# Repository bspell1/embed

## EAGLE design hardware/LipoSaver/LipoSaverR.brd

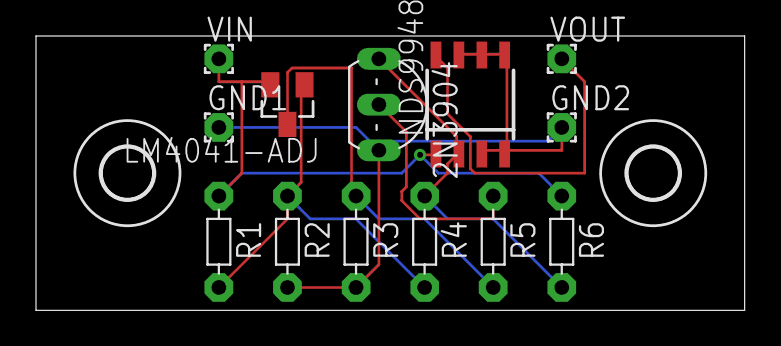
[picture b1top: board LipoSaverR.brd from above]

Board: 2 copper layers, 39.4 x 15.2 mm, 15 parts (0 on the bottom side), 7 nets.

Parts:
2N3904: TO92-EBC
E$40, E$42: 2,8
GND1, GND2: 1,6/0,8
LM4041-ADJ: SOT23
NDS9948: SOIC8
R1: R1; R-5
R2: R2; R-5
R3: 10K; R-5
R4: 4.7M; R-5
R5: 100K; R-5
R6: 20K; R-5
VIN: 1,6/0,8
VOUT: 1,6/0,8

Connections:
S$1: 2N3904.E, GND1.1, GND2.1, NDS9948.3, NDS9948.4, NDS9948.5, NDS9948.6, NDS9948.7, R2.2, R3.2
S$2: LM4041-ADJ.2, NDS9948.1, R1.1, R6.1, VIN.1
S$3: LM4041-ADJ.3, R3.1, R5.2
S$4: 2N3904.C, NDS9948.2, R4.1, R6.2
S$5: 2N3904.B, R5.1
S$6: NDS9948.8, VOUT.1
S$11: LM4041-ADJ.1, R1.2, R2.1, R4.2

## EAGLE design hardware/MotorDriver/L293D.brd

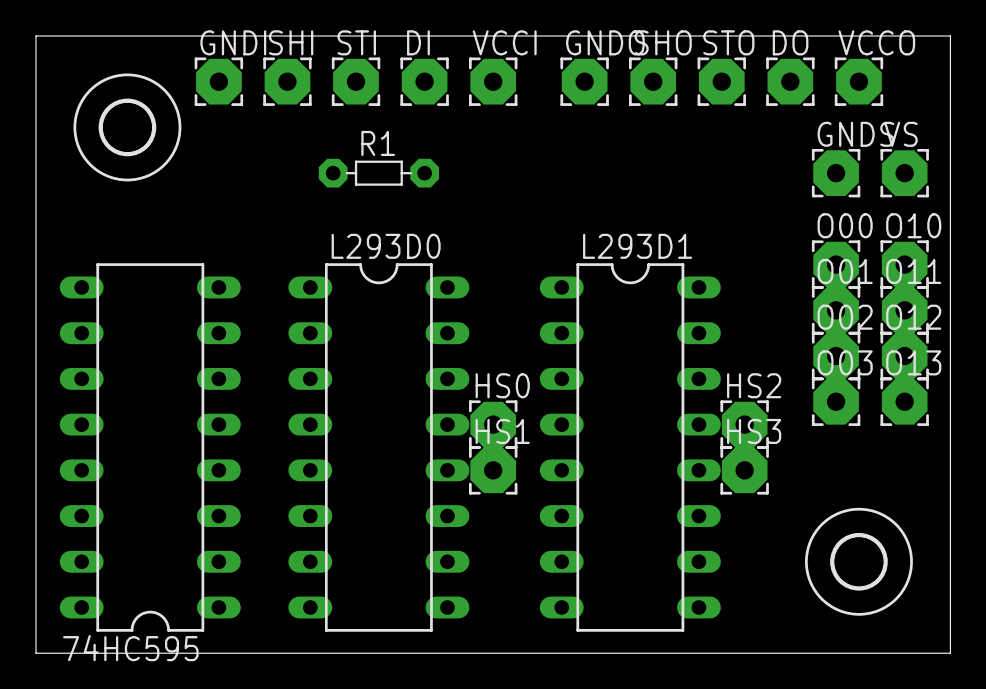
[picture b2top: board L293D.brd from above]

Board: 2 copper layers, 50.8 x 34.3 mm, 30 parts (0 on the bottom side), 24 nets, no tracks yet.

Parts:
74HC595: DIL16
DI: 2,54/1,0
DO: 2,54/1,0
E$1, E$2: 2,8
GNDI: 2,54/1,0
GNDO: 2,54/1,0
GNDS: 2,54/1,0
HS0, HS1, HS2, HS3: 2,54/1,0
L293D0, L293D1: DIL16
O00, O01, O02, O03, O10, O11, O12, O13: 2,54/1,0
R1: 10K; R-5
SHI: 2,54/1,0
SHO: 2,54/1,0
STI: 2,54/1,0
STO: 2,54/1,0
VCCI: 2,54/1,0
VCCO: 2,54/1,0
VS: 2,54/1,0

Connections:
GND: 74HC595.8, 74HC595.13, GNDI.1, GNDO.1, GNDS.1, HS0.1, HS1.1, HS2.1, HS3.1, L293D0.4, L293D0.5, L293D0.12, L293D0.13, L293D1.4, L293D1.5, L293D1.12, L293D1.13
S$1: 74HC595.10, L293D0.1, L293D0.9, L293D1.1, L293D1.9, R1.2
S$2: 74HC595.11, SHI.1, SHO.1
S$3: 74HC595.12, STI.1, STO.1
S$4: L293D0.8, L293D1.8, VS.1
S$5: 74HC595.14, DI.1
S$6: 74HC595.9, DO.1
S$7: 74HC595.15, L293D0.2
S$8: 74HC595.1, L293D0.7
S$9: 74HC595.2, L293D0.10
S$10: 74HC595.3, L293D0.15
S$11: L293D0.3, O00.1
S$12: L293D0.6, O01.1
S$13: L293D0.11, O02.1
S$14: L293D0.14, O03.1
S$15: 74HC595.4, L293D1.2
S$16: 74HC595.5, L293D1.7
S$17: 74HC595.6, L293D1.10
S$18: 74HC595.7, L293D1.15
S$19: L293D1.3, O10.1
S$20: L293D1.6, O11.1
S$21: L293D1.11, O12.1
S$22: L293D1.14, O13.1
W1: 74HC595.16, L293D0.16, L293D1.16, R1.1, VCCI.1, VCCO.1

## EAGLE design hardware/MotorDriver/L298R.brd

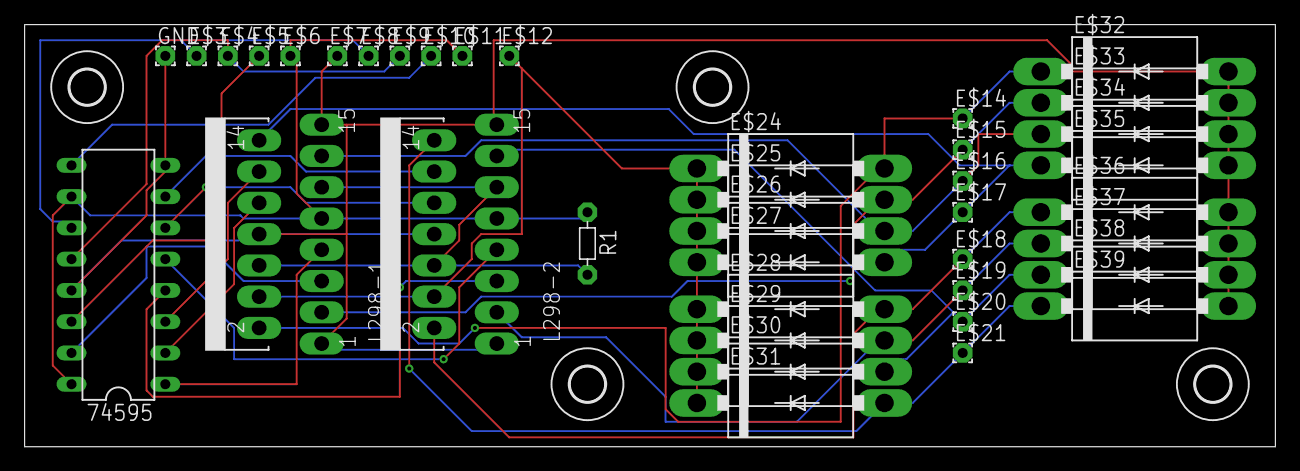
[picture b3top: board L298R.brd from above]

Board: 2 copper layers, 101.6 x 34.3 mm, 43 parts (0 on the bottom side), 24 nets.

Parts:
74595: 74595; DIL16
E$1, E$40, E$41, E$42: 2,8
E$3, E$4, E$5, E$6, E$7, E$8, E$9, E$10, E$11, E$12, E$14, E$15, E$16, E$17, E$18, E$19, E$20, E$21: 1,6/0,8
E$24, E$25, E$26, E$27, E$28, E$29, E$30, E$31, E$32, E$33, E$34, E$35, E$36, E$37, E$38, E$39: DO201-15
GND: 1,6/0,8
L298-1, L298-2: L298; MULTIWATT-15
R1: 10K; R-5

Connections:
S$1: 74595.8, 74595.13, E$7.1, E$32.A, E$33.A, E$34.A, E$35.A, E$36.A, E$37.A, E$38.A, E$39.A, GND.1, L298-1.1, L298-1.8, L298-1.15, L298-2.1, L298-2.8, L298-2.15
S$2: 74595.10, 74595.16, E$6.1, E$11.1, L298-1.9, L298-2.9, R1.1
S$3: 74595.11, E$3.1, E$8.1
S$4: 74595.12, E$4.1, E$9.1
S$5: 74595.14, E$5.1
S$6: 74595.9, E$10.1
S$7: E$14.1, E$24.A, E$32.C, L298-1.2
S$8: E$15.1, E$25.A, E$33.C, L298-1.3
S$9: E$12.1, E$24.C, E$25.C, E$26.C, E$27.C, E$28.C, E$29.C, E$30.C, E$31.C, L298-1.4, L298-2.4
S$10: 74595.15, L298-1.5
S$11: L298-1.6, L298-1.11, L298-2.6, L298-2.11, R1.2
S$12: 74595.1, L298-1.7
S$13: 74595.2, L298-1.10
S$14: 74595.3, L298-1.12
S$15: E$16.1, E$26.A, E$34.C, L298-1.13
S$16: E$17.1, E$27.A, E$35.C, L298-1.14
S$17: E$18.1, E$28.A, E$36.C, L298-2.2
S$18: E$19.1, E$29.A, E$37.C, L298-2.3
S$19: E$20.1, E$30.A, E$38.C, L298-2.13
S$20: E$21.1, E$31.A, E$39.C, L298-2.14
S$21: 74595.4, L298-2.5
S$22: 74595.5, L298-2.7
S$23: 74595.6, L298-2.10
S$24: 74595.7, L298-2.12

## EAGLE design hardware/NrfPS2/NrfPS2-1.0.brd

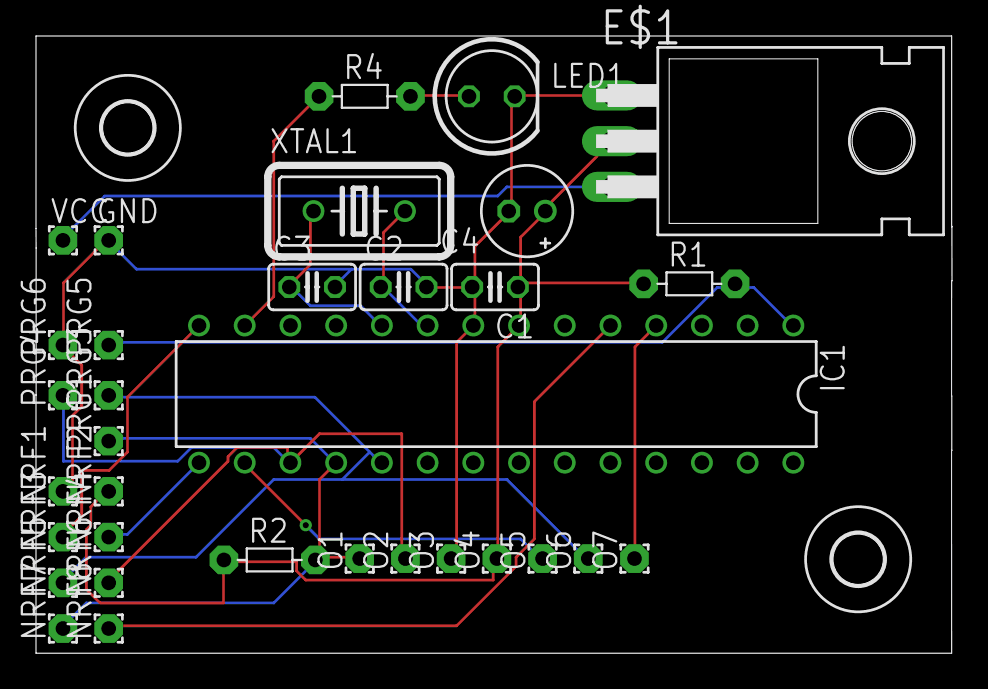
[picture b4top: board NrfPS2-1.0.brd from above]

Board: 2 copper layers, 50.9 x 34.3 mm, 35 parts (0 on the bottom side), 16 nets.

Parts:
C1, C2, C3: C025-025X050
C4: E2-5
E$1: TO220H
E$2, E$14: 2,8
GND: 1,6/0,8
IC1: PDIP-T28
LED1: LED5MM
NRF1, NRF2, NRF3, NRF4, NRF5, NRF6, NRF7, NRF8: 1,6/0,8
O1, O2, O3, O4, O5, O6, O7: 1,6/0,8
PRG1, PRG3, PRG4, PRG5, PRG6: 1,6/0,8
R1, R2, R4: R-5
VCC: 1,6/0,8
XTAL1: HC18U-V

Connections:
S$2: C1.2, C2.2, C3.2, C4.-, E$1.1, GND.1, IC1.8, LED1.K, NRF1.1, O3.1, PRG6.1
S$3: E$1.3, VCC.1
S$5: IC1.13, R4.1
S$6: C2.1, IC1.9, XTAL1.2
S$7: C3.1, IC1.10, XTAL1.1
S$8: IC1.1, PRG5.1, R1.2
S$9: IC1.18, NRF7.1, O1.1, PRG1.1, R2.2
S$10: C1.1, C4.+, E$1.2, IC1.7, NRF2.1, O4.1, R1.1, R2.1
S$11: IC1.15, NRF4.1
S$12: IC1.19, NRF5.1, O6.1, PRG3.1
S$13: IC1.17, NRF6.1, O2.1, PRG4.1
S$14: IC1.14, NRF3.1
S$15: IC1.16, O5.1
S$16: IC1.4, O7.1
S$18: IC1.5, NRF8.1
S$22: LED1.A, R4.2

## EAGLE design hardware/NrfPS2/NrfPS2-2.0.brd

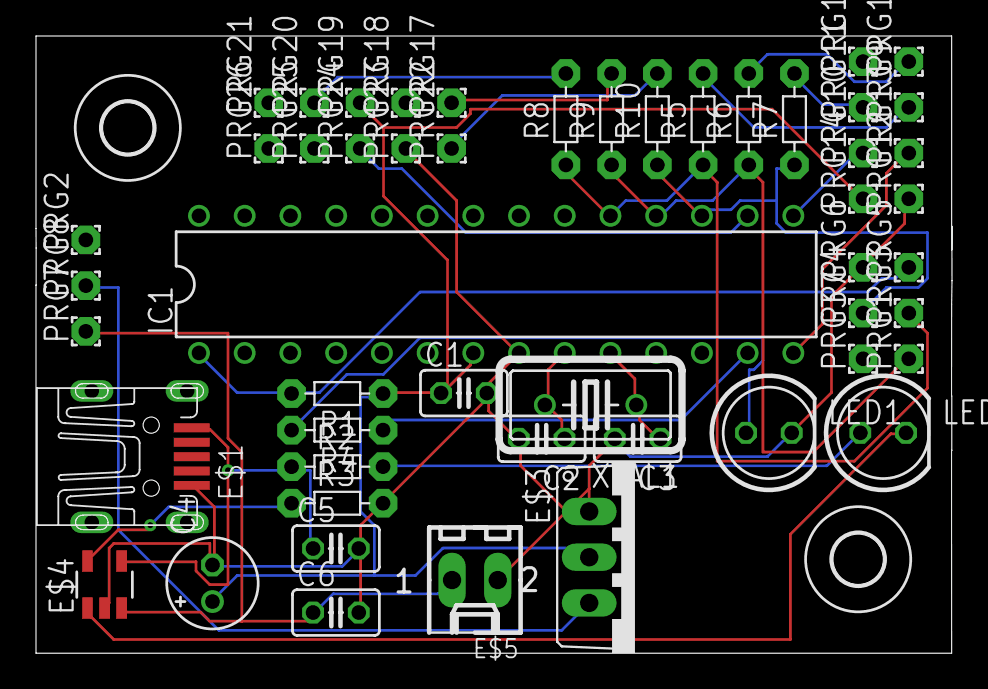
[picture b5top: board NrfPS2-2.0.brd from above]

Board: 2 copper layers, 50.9 x 34.3 mm, 53 parts (0 on the bottom side), 25 nets.

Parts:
C1, C2, C3, C5, C6: C025-025X050
C4: E2-5
E$1: UX60-MB-5S8
E$2, E$14: 2,8
E$3: TO220V
E$4: SOT23-5
E$5: 6410-02
IC1: PDIP-T28
LED1, LED2: LED5MM
PRG1, PRG2, PRG3, PRG4, PRG5, PRG6, PRG7, PRG8, PRG9, PRG10, PRG11, PRG12, PRG13, PRG14, PRG15, PRG16, PRG17, PRG18, PRG19, PRG20, PRG21, PRG22, PRG23, PRG24, PRG25, PRG26, PRG37: 1,6/0,8
R1, R2, R3, R4, R5, R6, R7, R8, R9, R10: R-5
XTAL1: HC18U-V

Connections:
S$2: C1.2, C2.2, C3.2, C4.-, C5.2, C6.2, E$1.5, E$3.1, E$4.2, E$5.2, IC1.8, LED1.K, PRG6.1, PRG12.1, PRG23.1, R3.2
S$3: E$4.1, LED2.K
S$5: IC1.13, R4.1
S$6: C2.1, IC1.9, XTAL1.2
S$7: C3.1, IC1.10, XTAL1.1
S$8: IC1.1, PRG5.1, R1.2
S$9: IC1.18, PRG1.1, R6.1, R9.1
S$10: C1.1, C4.+, E$3.2, IC1.7, PRG14.1, PRG19.1, R1.1
S$11: IC1.15, PRG10.1
S$12: IC1.19, PRG3.1, R5.1, R8.1
S$13: IC1.17, PRG4.1, R7.1, R10.1
S$14: IC1.14, PRG13.1
S$15: IC1.16, PRG24.1
S$20: E$3.3, PRG8.1
S$22: LED1.A, R4.2
S$33: LED2.A, R2.2
S$35: C5.1, E$1.1, E$4.4, R2.1
S$36: E$4.5, R3.1
S$37: PRG9.1, R5.2
S$38: PRG11.1, R7.2
S$39: PRG15.1, R6.2
S$40: PRG17.1, R9.2
S$41: PRG22.1, R10.2
S$42: PRG20.1, R8.2
S$43: C6.1, E$4.3, E$5.1, PRG7.1
